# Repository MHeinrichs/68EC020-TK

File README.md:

[This project moved to gitlab on the day M$ bought github](https://gitlab.com/MHeinrichs/68EC020-TK)

The new repository is at: https://gitlab.com/MHeinrichs/68EC020-TK

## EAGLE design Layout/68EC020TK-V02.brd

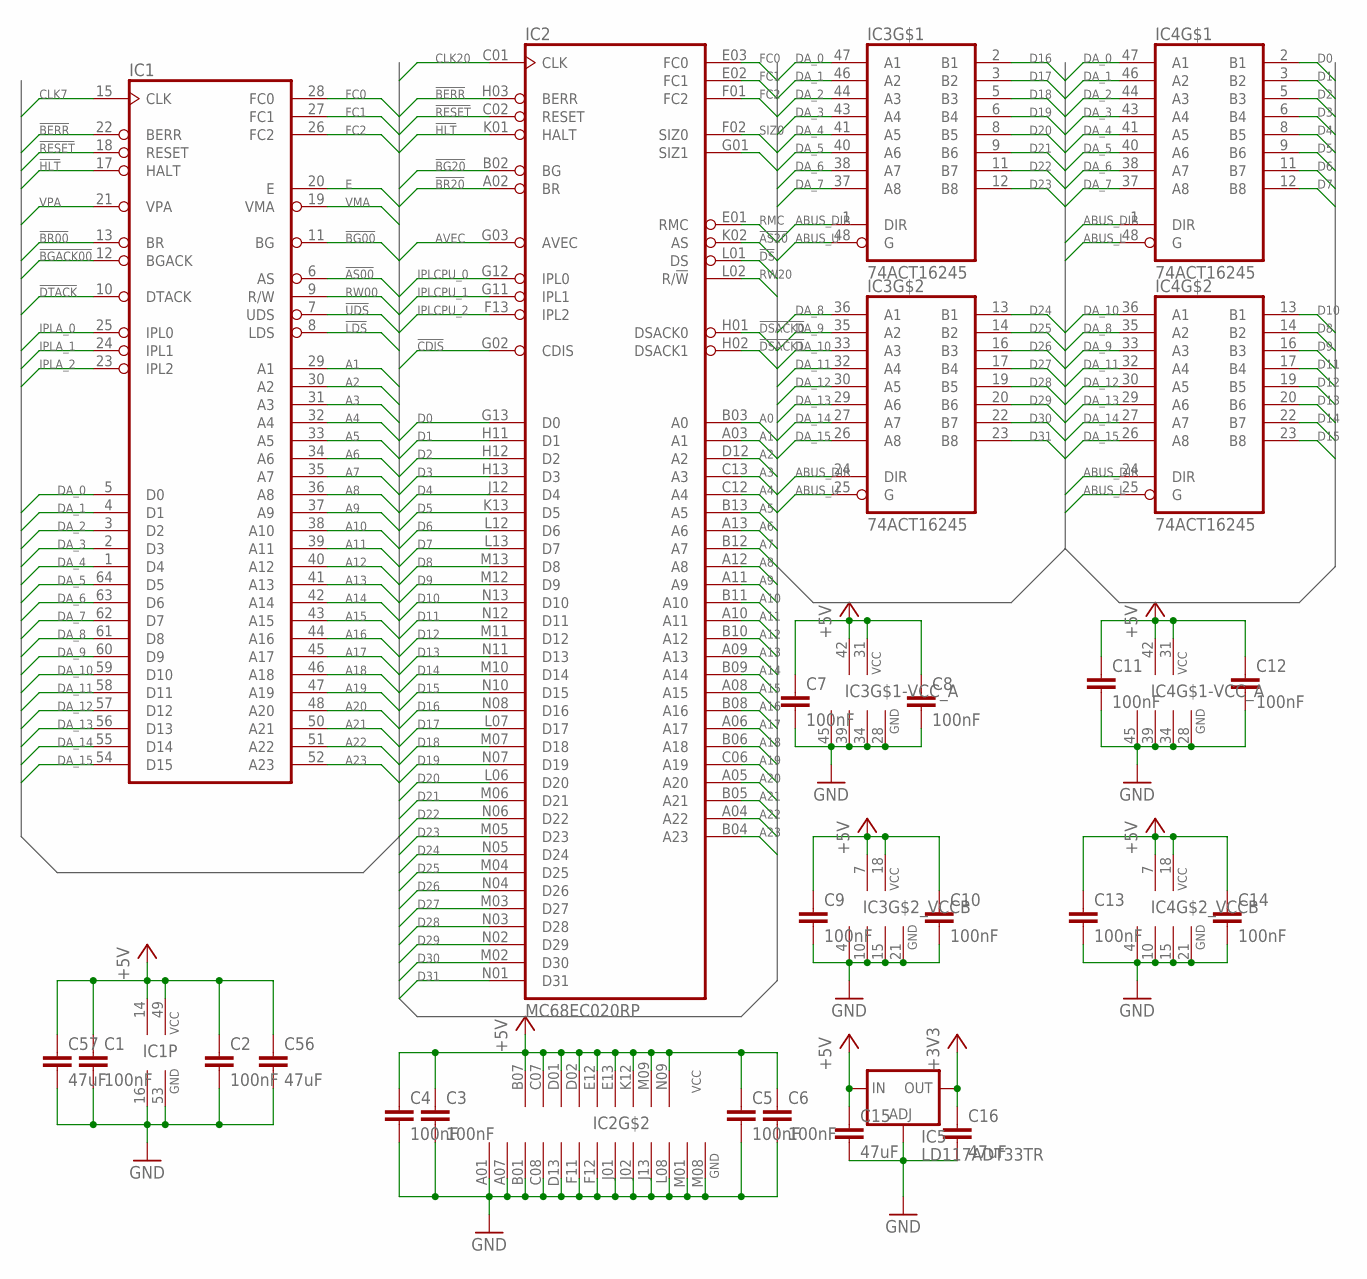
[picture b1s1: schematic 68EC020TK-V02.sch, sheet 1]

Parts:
C1, C2, C3, C4, C5, C6, C7, C8, C9, C10, C11, C12, C13, C14: 100nF; C0603K
C15, C16, C56, C57: 47uF; C1206K
IC1: MC68000PROUND-PADS; DIL64-ROUND
IC2: MC68EC020RP; MPGA114EC
IC3, IC4: 74ACT16245; TSSOP48
IC5: LD117ADT33TR; DPACK

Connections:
!AS00: IC1.6 (AS); also elsewhere on the board
!AS20: IC2.K02 (AS); also elsewhere on the board
!BERR: IC1.22 (BERR), IC2.H03 (BERR); also elsewhere on the board
!BG00: IC1.11 (BG); also elsewhere on the board
!BG20: IC2.B02 (BG); also elsewhere on the board
!BGACK00: IC1.12 (BGACK); also elsewhere on the board
!BR00: IC1.13 (BR); also elsewhere on the board
!BR20: IC2.A02 (BR); also elsewhere on the board
!CDIS: IC2.G02 (CDIS); also elsewhere on the board
!DS: IC2.L01 (DS); also elsewhere on the board
!DSACK0: IC2.H01 (DSACK0); also elsewhere on the board
!DSACK1: IC2.H02 (DSACK1); also elsewhere on the board
!DTACK: IC1.10 (DTACK); also elsewhere on the board
!HLT: IC1.17 (HALT), IC2.K01 (HALT)
!LDS: IC1.8 (LDS); also elsewhere on the board
!RESET: IC1.18 (RESET), IC2.C02 (RESET); also elsewhere on the board
!UDS: IC1.7 (UDS); also elsewhere on the board
+3V3: C16.1, IC5.4 (OUT); also elsewhere on the board
+5V: C1.1, C2.1, C3.1, C4.1, C5.1, C6.1, C7.1, C8.1, C9.1, C10.1, C11.1, C12.1, C13.1, C14.1, C15.1, C56.1, C57.1, IC1.14 (VCC), IC1.49 (VCC), IC2.B07 (VCC), IC2.C07 (VCC), IC2.D01 (VCC), IC2.D02 (VCC), IC2.E12 (VCC), IC2.E13 (VCC), IC2.K12 (VCC), IC2.M09 (VCC), IC2.N09 (VCC), IC3.7 (VCC), IC3.18 (VCC), IC3.31 (VCC), IC3.42 (VCC), IC4.7 (VCC), IC4.18 (VCC), IC4.31 (VCC), IC4.42 (VCC), IC5.3 (IN); also elsewhere on the board
A0: IC2.B03 (A0); also elsewhere on the board
A1: IC1.29 (A1), IC2.A03 (A1); also elsewhere on the board
A2: IC1.30 (A2), IC2.D12 (A2); also elsewhere on the board
A3: IC1.31 (A3), IC2.C13 (A3); also elsewhere on the board
A4: IC1.32 (A4), IC2.C12 (A4); also elsewhere on the board
A5: IC1.33 (A5), IC2.B13 (A5); also elsewhere on the board
A6: IC1.34 (A6), IC2.A13 (A6); also elsewhere on the board
A7: IC1.35 (A7), IC2.B12 (A7); also elsewhere on the board
A8: IC1.36 (A8), IC2.A12 (A8); also elsewhere on the board
A9: IC1.37 (A9), IC2.A11 (A9); also elsewhere on the board
A10: IC1.38 (A10), IC2.B11 (A10); also elsewhere on the board
A11: IC1.39 (A11), IC2.A10 (A11); also elsewhere on the board
A12: IC1.40 (A12), IC2.B10 (A12); also elsewhere on the board
A13: IC1.41 (A13), IC2.A09 (A13); also elsewhere on the board
A14: IC1.42 (A14), IC2.B09 (A14); also elsewhere on the board
A15: IC1.43 (A15), IC2.A08 (A15); also elsewhere on the board
A16: IC1.44 (A16), IC2.B08 (A16); also elsewhere on the board
A17: IC1.45 (A17), IC2.A06 (A17); also elsewhere on the board
A18: IC1.46 (A18), IC2.B06 (A18); also elsewhere on the board
A19: IC1.47 (A19), IC2.C06 (A19); also elsewhere on the board
A20: IC1.48 (A20), IC2.A05 (A20); also elsewhere on the board
A21: IC1.50 (A21), IC2.B05 (A21); also elsewhere on the board
A22: IC1.51 (A22), IC2.A04 (A22); also elsewhere on the board
A23: IC1.52 (A23), IC2.B04 (A23); also elsewhere on the board
ABUS_DIR: IC3.1 (DIR), IC3.24 (DIR), IC4.1 (DIR), IC4.24 (DIR); also elsewhere on the board
ABUS_L: IC4.25 (G), IC4.48 (G); also elsewhere on the board
ABUS_U: IC3.25 (G), IC3.48 (G); also elsewhere on the board
AVEC: IC2.G03 (AVEC); also elsewhere on the board
CLK7: IC1.15 (CLK); also elsewhere on the board
CLK20: IC2.C01 (CLK); also elsewhere on the board
D0: IC2.G13 (D0), IC4.2 (B1); also elsewhere on the board
D1: IC2.H11 (D1), IC4.3 (B2); also elsewhere on the board
D2: IC2.H12 (D2), IC4.5 (B3); also elsewhere on the board
D3: IC2.H13 (D3), IC4.6 (B4); also elsewhere on the board
D4: IC2.J12 (D4), IC4.8 (B5); also elsewhere on the board
D5: IC2.K13 (D5), IC4.9 (B6); also elsewhere on the board
D6: IC2.L12 (D6), IC4.11 (B7); also elsewhere on the board
D7: IC2.L13 (D7), IC4.12 (B8); also elsewhere on the board
D8: IC2.M13 (D8), IC4.14 (B2); also elsewhere on the board
D9: IC2.M12 (D9), IC4.16 (B3); also elsewhere on the board
D10: IC2.N13 (D10), IC4.13 (B1); also elsewhere on the board
D11: IC2.N12 (D11), IC4.17 (B4); also elsewhere on the board
D12: IC2.M11 (D12), IC4.19 (B5); also elsewhere on the board
D13: IC2.N11 (D13), IC4.20 (B6); also elsewhere on the board
D14: IC2.M10 (D14), IC4.22 (B7); also elsewhere on the board
D15: IC2.N10 (D15), IC4.23 (B8); also elsewhere on the board
D16: IC2.N08 (D16), IC3.2 (B1); also elsewhere on the board
D17: IC2.L07 (D17), IC3.3 (B2); also elsewhere on the board
D18: IC2.M07 (D18), IC3.5 (B3); also elsewhere on the board
D19: IC2.N07 (D19), IC3.6 (B4); also elsewhere on the board
D20: IC2.L06 (D20), IC3.8 (B5); also elsewhere on the board
D21: IC2.M06 (D21), IC3.9 (B6); also elsewhere on the board
D22: IC2.N06 (D22), IC3.11 (B7); also elsewhere on the board
D23: IC2.M05 (D23), IC3.12 (B8); also elsewhere on the board
D24: IC2.N05 (D24), IC3.13 (B1); also elsewhere on the board
D25: IC2.M04 (D25), IC3.14 (B2); also elsewhere on the board
D26: IC2.N04 (D26), IC3.16 (B3); also elsewhere on the board
D27: IC2.M03 (D27), IC3.17 (B4); also elsewhere on the board
D28: IC2.N03 (D28), IC3.19 (B5); also elsewhere on the board
D29: IC2.N02 (D29), IC3.20 (B6); also elsewhere on the board
D30: IC2.M02 (D30), IC3.22 (B7); also elsewhere on the board
D31: IC2.N01 (D31), IC3.23 (B8); also elsewhere on the board
DA_0: IC1.5 (D0), IC3.47 (A1), IC4.47 (A1)
DA_1: IC1.4 (D1), IC3.46 (A2), IC4.46 (A2)
DA_2: IC1.3 (D2), IC3.44 (A3), IC4.44 (A3)
DA_3: IC1.2 (D3), IC3.43 (A4), IC4.43 (A4)
DA_4: IC1.1 (D4), IC3.41 (A5), IC4.41 (A5)
DA_5: IC1.64 (D5), IC3.40 (A6), IC4.40 (A6)
DA_6: IC1.63 (D6), IC3.38 (A7), IC4.38 (A7)
DA_7: IC1.62 (D7), IC3.37 (A8), IC4.37 (A8)
DA_8: IC1.61 (D8), IC3.36 (A1), IC4.35 (A2)
DA_9: IC1.60 (D9), IC3.35 (A2), IC4.33 (A3)
DA_10: IC1.59 (D10), IC3.33 (A3), IC4.36 (A1)
DA_11: IC1.58 (D11), IC3.32 (A4), IC4.32 (A4)
DA_12: IC1.57 (D12), IC3.30 (A5), IC4.30 (A5)
DA_13: IC1.56 (D13), IC3.29 (A6), IC4.29 (A6)
DA_14: IC1.55 (D14), IC3.27 (A7), IC4.27 (A7)
DA_15: IC1.54 (D15), IC3.26 (A8), IC4.26 (A8)
E: IC1.20 (E); also elsewhere on the board
FC0: IC1.28 (FC0), IC2.E03 (FC0); also elsewhere on the board
FC1: IC1.27 (FC1), IC2.E02 (FC1); also elsewhere on the board
FC2: IC1.26 (FC2), IC2.F01 (FC2)
GND: C1.2, C2.2, C3.2, C4.2, C5.2, C6.2, C7.2, C8.2, C9.2, C10.2, C11.2, C12.2, C13.2, C14.2, C15.2, C16.2, C56.2, C57.2, IC1.16 (GND), IC1.53 (GND), IC2.A01 (GND), IC2.A07 (GND), IC2.B01 (GND), IC2.C08 (GND), IC2.D13 (GND), IC2.F11 (GND), IC2.F12 (GND), IC2.J01 (GND), IC2.J02 (GND), IC2.J13 (GND), IC2.L08 (GND), IC2.M01 (GND), IC2.M08 (GND), IC3.4 (GND), IC3.10 (GND), IC3.15 (GND), IC3.21 (GND), IC3.28 (GND), IC3.34 (GND), IC3.39 (GND), IC3.45 (GND), IC4.4 (GND), IC4.10 (GND), IC4.15 (GND), IC4.21 (GND), IC4.28 (GND), IC4.34 (GND), IC4.39 (GND), IC4.45 (GND), IC5.1 (ADJ); also elsewhere on the board
IPLA_0: IC1.25 (IPL0); also elsewhere on the board
IPLA_1: IC1.24 (IPL1); also elsewhere on the board
IPLA_2: IC1.23 (IPL2); also elsewhere on the board
IPLCPU_0: IC2.G12 (IPL0); also elsewhere on the board
IPLCPU_1: IC2.G11 (IPL1); also elsewhere on the board
IPLCPU_2: IC2.F13 (IPL2); also elsewhere on the board
RMC: IC2.E01 (RMC); also elsewhere on the board
RW00: IC1.9 (R/W); also elsewhere on the board
RW20: IC2.L02 (R/!W); also elsewhere on the board
SIZ0: IC2.F02 (SIZ0); also elsewhere on the board
SIZ1: IC2.G01 (SIZ1); also elsewhere on the board
VMA: IC1.19 (VMA); also elsewhere on the board
VPA: IC1.21 (VPA); also elsewhere on the board

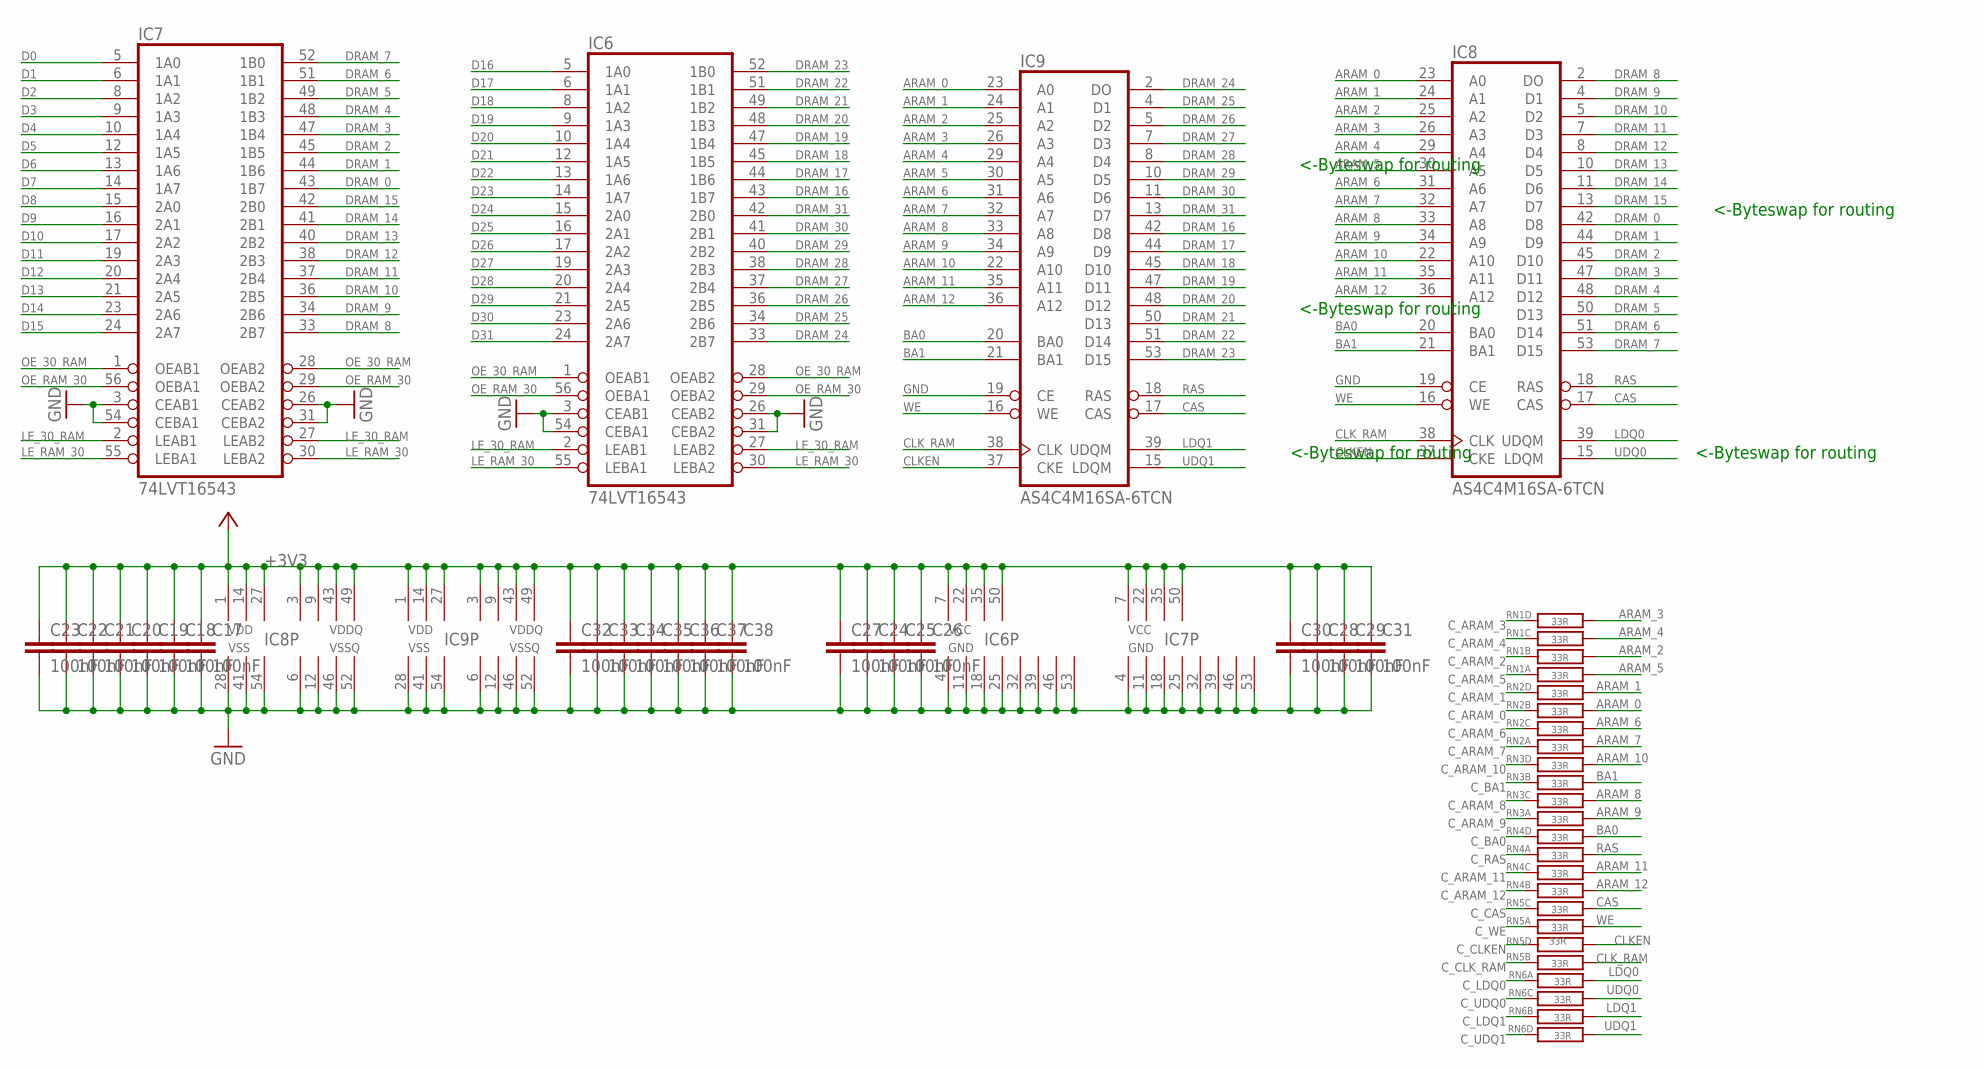
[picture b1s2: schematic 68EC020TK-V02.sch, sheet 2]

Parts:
C17, C18, C19, C20, C21, C22, C23, C24, C25, C26, C27, C28, C29, C30, C31, C32, C33, C34, C35, C36, C37, C38: 100nF; C0603K
IC6, IC7: 74LVT16543; TSSOP56@2
IC8, IC9: AS4C4M16SA-6TCN; TSOP2-54@2
RN1, RN2, RN3, RN4, RN5, RN6: 33R; R-NETZ@2

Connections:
+3V3: C17.1, C18.1, C19.1, C20.1, C21.1, C22.1, C23.1, C24.1, C25.1, C26.1, C27.1, C28.1, C29.1, C30.1, C31.1, C32.1, C33.1, C34.1, C35.1, C36.1, C37.1, C38.1, IC6.7 (VCC), IC6.22 (VCC), IC6.35 (VCC), IC6.50 (VCC), IC7.7 (VCC), IC7.22 (VCC), IC7.35 (VCC), IC7.50 (VCC), IC8.1 (VCC), IC8.3 (VCC), IC8.9 (VCC), IC8.14 (VCC), IC8.27 (VCC), IC8.43 (VCC), IC8.49 (VCC), IC9.1 (VCC), IC9.3 (VCC), IC9.9 (VCC), IC9.14 (VCC), IC9.27 (VCC), IC9.43 (VCC), IC9.49 (VCC); also elsewhere on the board
ARAM_0: IC8.23 (A0), IC9.23 (A0), RN2.P$2
ARAM_1: IC8.24 (A1), IC9.24 (A1), RN2.P$4
ARAM_2: IC8.25 (A2), IC9.25 (A2), RN1.P$2
ARAM_3: IC8.26 (A3), IC9.26 (A3), RN1.P$4
ARAM_4: IC8.29 (A4), IC9.29 (A4), RN1.P$3
ARAM_5: IC8.30 (A5), IC9.30 (A5), RN1.P$1
ARAM_6: IC8.31 (A6), IC9.31 (A6), RN2.P$3
ARAM_7: IC8.32 (A7), IC9.32 (A7), RN2.P$1
ARAM_8: IC8.33 (A8), IC9.33 (A8), RN3.P$3
ARAM_9: IC8.34 (A9), IC9.34 (A9), RN3.P$1
ARAM_10: IC8.22 (A10), IC9.22 (A10), RN3.P$4
ARAM_11: IC8.35 (A11), IC9.35 (A11), RN4.P$3
ARAM_12: IC8.36 (A12), IC9.36 (A12), RN4.P$2
BA0: IC8.20 (BA0), IC9.20 (BA0), RN4.P$4
BA1: IC8.21 (BA1), IC9.21 (BA1), RN3.P$2
CAS: IC8.17 (CAS), IC9.17 (CAS), RN5.P$3
CLKEN: IC8.37 (CKE), IC9.37 (CKE), RN5.P$4
CLK_RAM: IC8.38 (CLK), IC9.38 (CLK), RN5.P$2
C_ARAM_0: RN2.P$7; also elsewhere on the board
C_ARAM_1: RN2.P$5; also elsewhere on the board
C_ARAM_2: RN1.P$7; also elsewhere on the board
C_ARAM_3: RN1.P$5; also elsewhere on the board
C_ARAM_4: RN1.P$6; also elsewhere on the board
C_ARAM_5: RN1.P$8; also elsewhere on the board
C_ARAM_6: RN2.P$6; also elsewhere on the board
C_ARAM_7: RN2.P$8; also elsewhere on the board
C_ARAM_8: RN3.P$6; also elsewhere on the board
C_ARAM_9: RN3.P$8; also elsewhere on the board
C_ARAM_10: RN3.P$5; also elsewhere on the board
C_ARAM_11: RN4.P$6; also elsewhere on the board
C_ARAM_12: RN4.P$7; also elsewhere on the board
C_BA0: RN4.P$5; also elsewhere on the board
C_BA1: RN3.P$7; also elsewhere on the board
C_CAS: RN5.P$6; also elsewhere on the board
C_CLKEN: RN5.P$5; also elsewhere on the board
C_CLK_RAM: RN5.P$7; also elsewhere on the board
C_LDQ0: RN6.P$1; also elsewhere on the board
C_LDQ1: RN6.P$2; also elsewhere on the board
C_RAS: RN4.P$8; also elsewhere on the board
C_UDQ0: RN6.P$3; also elsewhere on the board
C_UDQ1: RN6.P$4; also elsewhere on the board
C_WE: RN5.P$8; also elsewhere on the board
D0: IC7.5 (1A0); also elsewhere on the board
D1: IC7.6 (1A1); also elsewhere on the board
D2: IC7.8 (1A2); also elsewhere on the board
D3: IC7.9 (1A3); also elsewhere on the board
D4: IC7.10 (1A4); also elsewhere on the board
D5: IC7.12 (1A5); also elsewhere on the board
D6: IC7.13 (1A6); also elsewhere on the board
D7: IC7.14 (1A7); also elsewhere on the board
D8: IC7.15 (2A0); also elsewhere on the board
D9: IC7.16 (2A1); also elsewhere on the board
D10: IC7.17 (2A2); also elsewhere on the board
D11: IC7.19 (2A3); also elsewhere on the board
D12: IC7.20 (2A4); also elsewhere on the board
D13: IC7.21 (2A5); also elsewhere on the board
D14: IC7.23 (2A6); also elsewhere on the board
D15: IC7.24 (2A7); also elsewhere on the board
D16: IC6.5 (1A0); also elsewhere on the board
D17: IC6.6 (1A1); also elsewhere on the board
D18: IC6.8 (1A2); also elsewhere on the board
D19: IC6.9 (1A3); also elsewhere on the board
D20: IC6.10 (1A4); also elsewhere on the board
D21: IC6.12 (1A5); also elsewhere on the board
D22: IC6.13 (1A6); also elsewhere on the board
D23: IC6.14 (1A7); also elsewhere on the board
D24: IC6.15 (2A0); also elsewhere on the board
D25: IC6.16 (2A1); also elsewhere on the board
D26: IC6.17 (2A2); also elsewhere on the board
D27: IC6.19 (2A3); also elsewhere on the board
D28: IC6.20 (2A4); also elsewhere on the board
D29: IC6.21 (2A5); also elsewhere on the board
D30: IC6.23 (2A6); also elsewhere on the board
D31: IC6.24 (2A7); also elsewhere on the board
DRAM_0: IC7.43 (1B7), IC8.42 (D8)
DRAM_1: IC7.44 (1B6), IC8.44 (D9)
DRAM_2: IC7.45 (1B5), IC8.45 (D10)
DRAM_3: IC7.47 (1B4), IC8.47 (D11)
DRAM_4: IC7.48 (1B3), IC8.48 (D12)
DRAM_5: IC7.49 (1B2), IC8.50 (D13)
DRAM_6: IC7.51 (1B1), IC8.51 (D14)
DRAM_7: IC7.52 (1B0), IC8.53 (D15)
DRAM_8: IC7.33 (2B7), IC8.2 (DO)
DRAM_9: IC7.34 (2B6), IC8.4 (D1)
DRAM_10: IC7.36 (2B5), IC8.5 (D2)
DRAM_11: IC7.37 (2B4), IC8.7 (D3)
DRAM_12: IC7.38 (2B3), IC8.8 (D4)
DRAM_13: IC7.40 (2B2), IC8.10 (D5)
DRAM_14: IC7.41 (2B1), IC8.11 (D6)
DRAM_15: IC7.42 (2B0), IC8.13 (D7)
DRAM_16: IC6.43 (1B7), IC9.42 (D8)
DRAM_17: IC6.44 (1B6), IC9.44 (D9)
DRAM_18: IC6.45 (1B5), IC9.45 (D10)
DRAM_19: IC6.47 (1B4), IC9.47 (D11)
DRAM_20: IC6.48 (1B3), IC9.48 (D12)
DRAM_21: IC6.49 (1B2), IC9.50 (D13)
DRAM_22: IC6.51 (1B1), IC9.51 (D14)
DRAM_23: IC6.52 (1B0), IC9.53 (D15)
DRAM_24: IC6.33 (2B7), IC9.2 (DO)
DRAM_25: IC6.34 (2B6), IC9.4 (D1)
DRAM_26: IC6.36 (2B5), IC9.5 (D2)
DRAM_27: IC6.37 (2B4), IC9.7 (D3)
DRAM_28: IC6.38 (2B3), IC9.8 (D4)
DRAM_29: IC6.40 (2B2), IC9.10 (D5)
DRAM_30: IC6.41 (2B1), IC9.11 (D6)
DRAM_31: IC6.42 (2B0), IC9.13 (D7)
GND: C17.2, C18.2, C19.2, C20.2, C21.2, C22.2, C23.2, C24.2, C25.2, C26.2, C27.2, C28.2, C29.2, C30.2, C31.2, C32.2, C33.2, C34.2, C35.2, C36.2, C37.2, C38.2, IC6.3 (CEAB1), IC6.4 (GND), IC6.11 (GND), IC6.18 (GND), IC6.25 (GND), IC6.26 (CEAB2), IC6.31 (CEBA2), IC6.32 (GND), IC6.39 (GND), IC6.46 (GND), IC6.53 (GND), IC6.54 (CEBA1), IC7.3 (CEAB1), IC7.4 (GND), IC7.11 (GND), IC7.18 (GND), IC7.25 (GND), IC7.26 (CEAB2), IC7.31 (CEBA2), IC7.32 (GND), IC7.39 (GND), IC7.46 (GND), IC7.53 (GND), IC7.54 (CEBA1), IC8.6 (GND), IC8.12 (GND), IC8.19 (CE), IC8.28 (GND), IC8.41 (GND), IC8.46 (GND), IC8.52 (GND), IC8.54 (GND), IC9.6 (GND), IC9.12 (GND), IC9.19 (CE), IC9.28 (GND), IC9.41 (GND), IC9.46 (GND), IC9.52 (GND), IC9.54 (GND); also elsewhere on the board
LDQ0: IC8.39 (UDQM), RN6.P$8
LDQ1: IC9.39 (UDQM), RN6.P$7
LE_30_RAM: IC6.2 (LEAB1), IC6.27 (LEAB2), IC7.2 (LEAB1), IC7.27 (LEAB2); also elsewhere on the board
LE_RAM_30: IC6.30 (LEBA2), IC6.55 (LEBA1), IC7.30 (LEBA2), IC7.55 (LEBA1); also elsewhere on the board
OE_30_RAM: IC6.1 (OEAB1), IC6.28 (OEAB2), IC7.1 (OEAB1), IC7.28 (OEAB2); also elsewhere on the board
OE_RAM_30: IC6.29 (OEBA2), IC6.56 (OEBA1), IC7.29 (OEBA2), IC7.56 (OEBA1); also elsewhere on the board
RAS: IC8.18 (RAS), IC9.18 (RAS), RN4.P$1
UDQ0: IC8.15 (LDQM), RN6.P$6
UDQ1: IC9.15 (LDQM), RN6.P$5
WE: IC8.16 (WE), IC9.16 (WE), RN5.P$1

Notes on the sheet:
<-Byteswap for routing

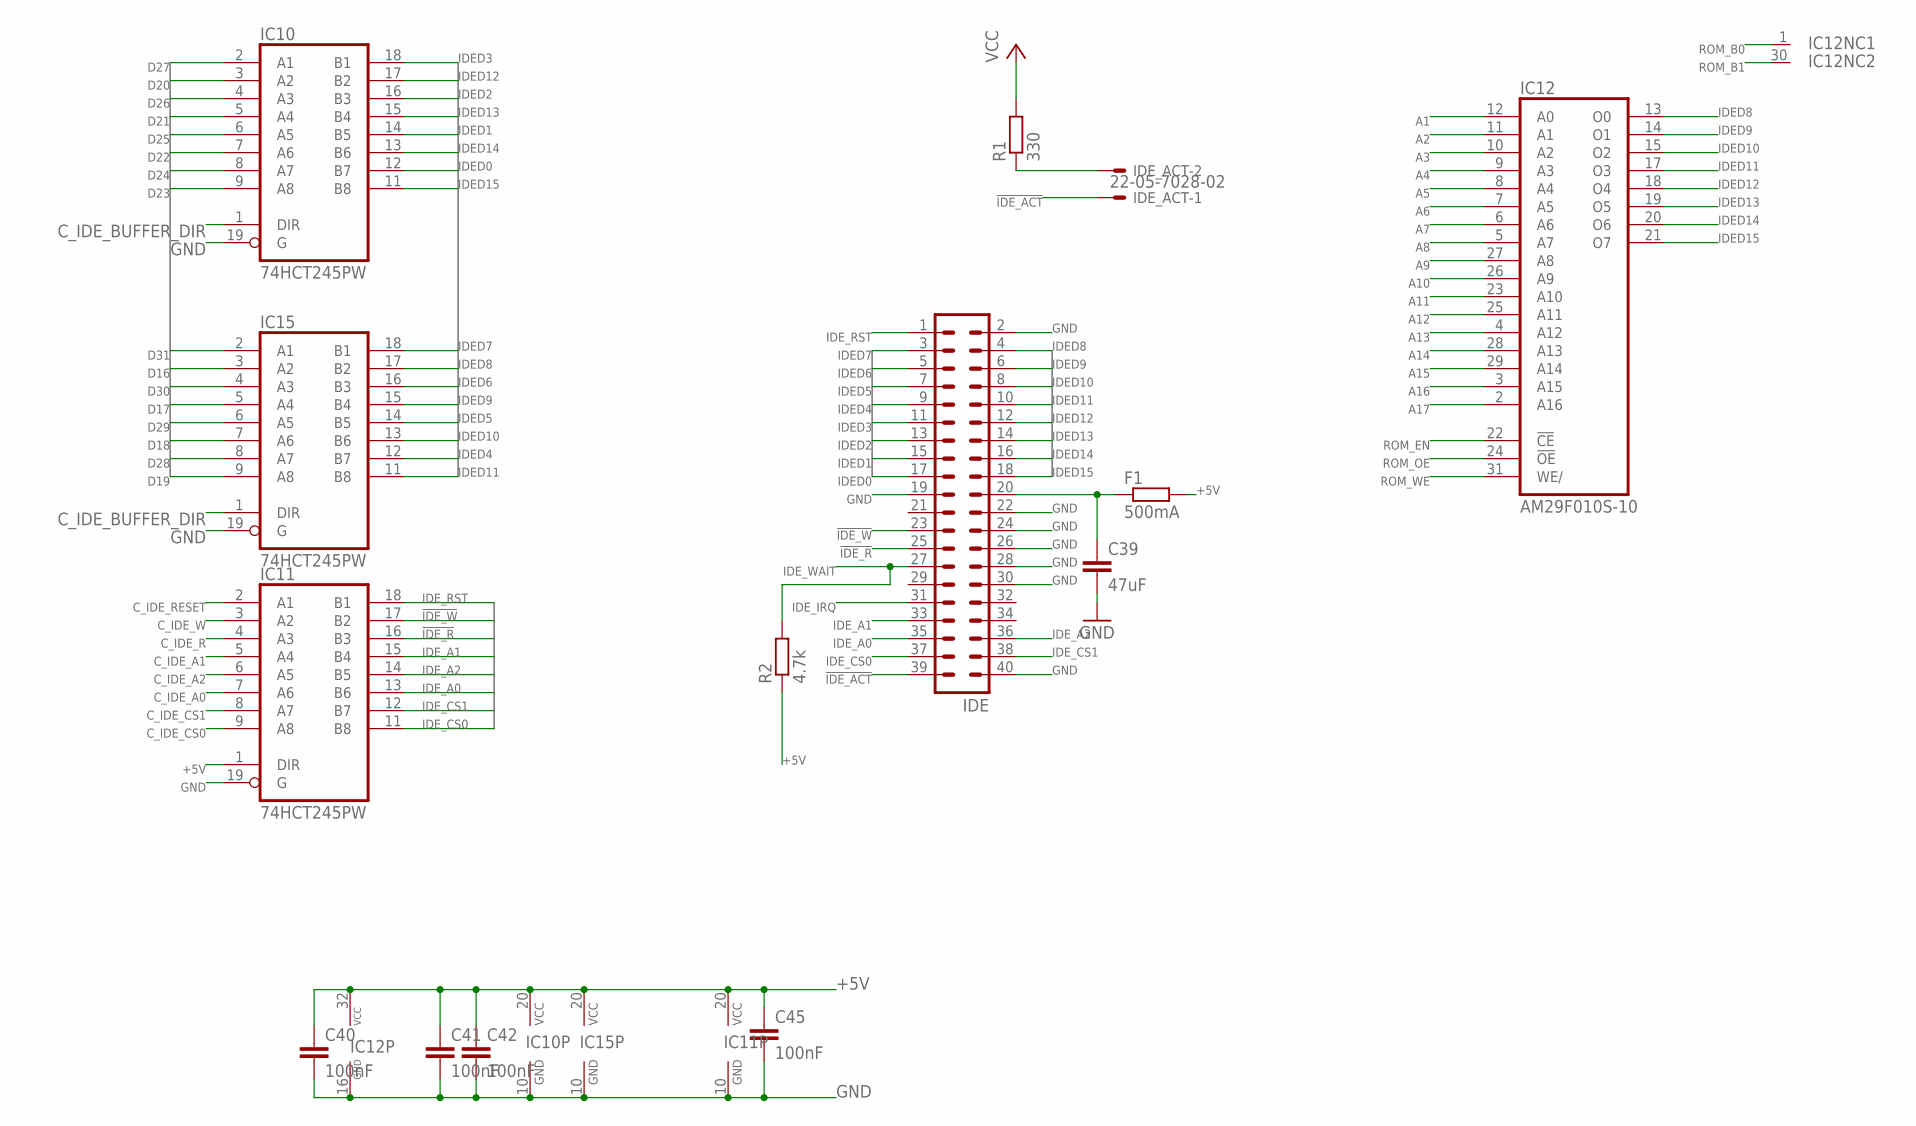
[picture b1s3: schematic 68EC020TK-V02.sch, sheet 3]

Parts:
C39: 47uF; C1206K
C40, C41, C42, C45: 100nF; C0603K
F1: 500mA; R2512
IC10, IC11, IC15: 74HCT245PW; TSSOP20
IC12: AM29F010S-10; PLCC-SR32
IDE: ML40
IDE_ACT: 22-05-7028-02; 7395-02
R1: 330; R0603
R2: 4.7k; R0603

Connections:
!IDE_ACT: IDE.39, IDE_ACT.1
!IDE_R: IC11.16 (B3), IDE.25
!IDE_W: IC11.17 (B2), IDE.23
+5V: C40.1, C41.1, C42.1, C45.1, F1.2, IC10.20 (VCC), IC11.1 (DIR), IC11.20 (VCC), IC12.32 (VCC), IC15.20 (VCC), R1.2, R2.1; also elsewhere on the board
A1: IC12.12 (A0); also elsewhere on the board
A2: IC12.11 (A1); also elsewhere on the board
A3: IC12.10 (A2); also elsewhere on the board
A4: IC12.9 (A3); also elsewhere on the board
A5: IC12.8 (A4); also elsewhere on the board
A6: IC12.7 (A5); also elsewhere on the board
A7: IC12.6 (A6); also elsewhere on the board
A8: IC12.5 (A7); also elsewhere on the board
A9: IC12.27 (A8); also elsewhere on the board
A10: IC12.26 (A9); also elsewhere on the board
A11: IC12.23 (A10); also elsewhere on the board
A12: IC12.25 (A11); also elsewhere on the board
A13: IC12.4 (A12); also elsewhere on the board
A14: IC12.28 (A13); also elsewhere on the board
A15: IC12.29 (A14); also elsewhere on the board
A16: IC12.3 (A15); also elsewhere on the board
A17: IC12.2 (A16); also elsewhere on the board
C_IDE_A0: IC11.7 (A6); also elsewhere on the board
C_IDE_A1: IC11.5 (A4); also elsewhere on the board
C_IDE_A2: IC11.6 (A5); also elsewhere on the board
C_IDE_BUFFER_DIR: IC10.1 (DIR), IC15.1 (DIR); also elsewhere on the board
C_IDE_CS0: IC11.9 (A8); also elsewhere on the board
C_IDE_CS1: IC11.8 (A7); also elsewhere on the board
C_IDE_R: IC11.4 (A3); also elsewhere on the board
C_IDE_RESET: IC11.2 (A1); also elsewhere on the board
C_IDE_W: IC11.3 (A2); also elsewhere on the board
D16: IC15.3 (A2); also elsewhere on the board
D17: IC15.5 (A4); also elsewhere on the board
D18: IC15.7 (A6); also elsewhere on the board
D19: IC15.9 (A8); also elsewhere on the board
D20: IC10.3 (A2); also elsewhere on the board
D21: IC10.5 (A4); also elsewhere on the board
D22: IC10.7 (A6); also elsewhere on the board
D23: IC10.9 (A8); also elsewhere on the board
D24: IC10.8 (A7); also elsewhere on the board
D25: IC10.6 (A5); also elsewhere on the board
D26: IC10.4 (A3); also elsewhere on the board
D27: IC10.2 (A1); also elsewhere on the board
D28: IC15.8 (A7); also elsewhere on the board
D29: IC15.6 (A5); also elsewhere on the board
D30: IC15.4 (A3); also elsewhere on the board
D31: IC15.2 (A1); also elsewhere on the board
GND: C39.2, C40.2, C41.2, C42.2, C45.2, IC10.10 (GND), IC10.19 (G), IC11.10 (GND), IC11.19 (G), IC12.16 (GND), IC15.10 (GND), IC15.19 (G), IDE.2, IDE.19, IDE.22, IDE.24, IDE.26, IDE.28, IDE.30, IDE.40; also elsewhere on the board
IDED0: IC10.12 (B7), IDE.17
IDED1: IC10.14 (B5), IDE.15
IDED2: IC10.16 (B3), IDE.13
IDED3: IC10.18 (B1), IDE.11
IDED4: IC15.12 (B7), IDE.9
IDED5: IC15.14 (B5), IDE.7
IDED6: IC15.16 (B3), IDE.5
IDED7: IC15.18 (B1), IDE.3
IDED8: IC12.13 (O0), IC15.17 (B2), IDE.4
IDED9: IC12.14 (O1), IC15.15 (B4), IDE.6
IDED10: IC12.15 (O2), IC15.13 (B6), IDE.8
IDED11: IC12.17 (O3), IC15.11 (B8), IDE.10
IDED12: IC10.17 (B2), IC12.18 (O4), IDE.12
IDED13: IC10.15 (B4), IC12.19 (O5), IDE.14
IDED14: IC10.13 (B6), IC12.20 (O6), IDE.16
IDED15: IC10.11 (B8), IC12.21 (O7), IDE.18
IDE_A0: IC11.13 (B6), IDE.35
IDE_A1: IC11.15 (B4), IDE.33
IDE_A2: IC11.14 (B5), IDE.36
IDE_CS0: IC11.11 (B8), IDE.37
IDE_CS1: IC11.12 (B7), IDE.38
IDE_IRQ: IDE.31
IDE_RST: IC11.18 (B1), IDE.1
IDE_WAIT: IDE.27, R2.2; also elsewhere on the board
KEY_PIN_POWER: C39.1, F1.1, IDE.20
unnamed: IDE_ACT.2, R1.1
ROM_B0: IC12.1 (NC); also elsewhere on the board
ROM_B1: IC12.30 (NC); also elsewhere on the board
ROM_EN: IC12.22 (!CE); also elsewhere on the board
ROM_OE: IC12.24 (!OE); also elsewhere on the board
ROM_WE: IC12.31 (WE/); also elsewhere on the board
